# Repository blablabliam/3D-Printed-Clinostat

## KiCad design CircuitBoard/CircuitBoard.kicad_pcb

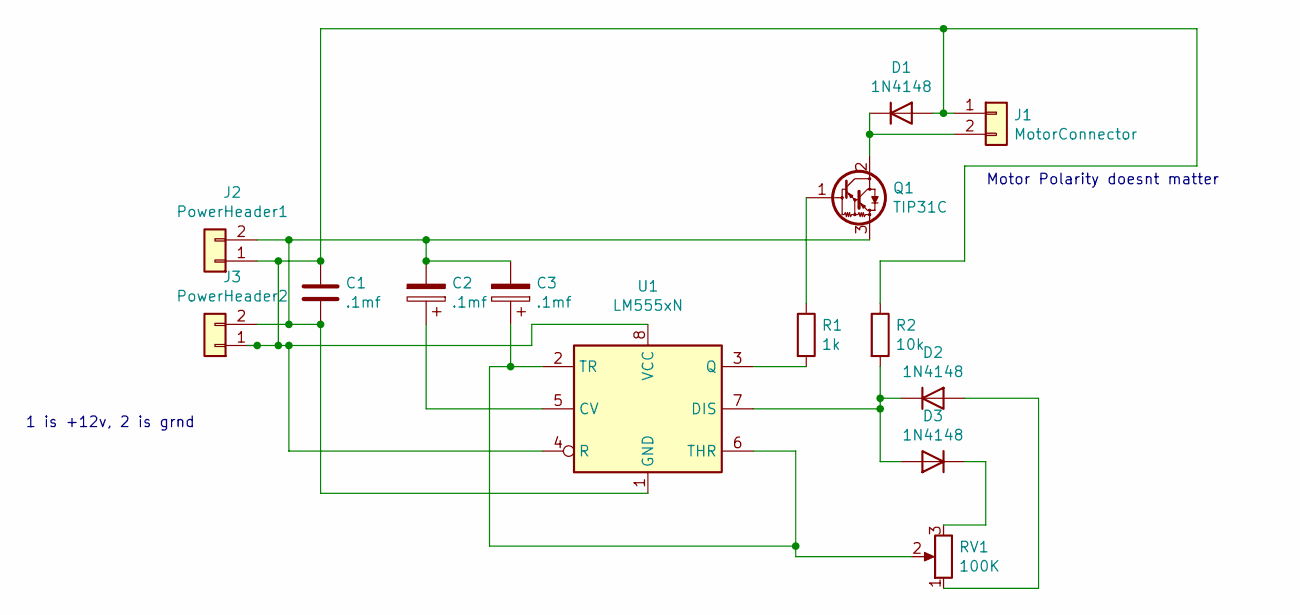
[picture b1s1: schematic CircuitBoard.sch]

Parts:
C1: .1mf; C_Disc_D6.0mm_W2.5mm_P5.00mm
C2, C3: .1mf; CP_Radial_D4.0mm_P2.00mm
D1, D2, D3: 1N4148; D_DO-35_SOD27_P7.62mm_Horizontal
J1: MotorConnector; PinHeader_1x02_P2.54mm_Vertical
J2: PowerHeader1; PinHeader_1x02_P2.54mm_Vertical
J3: PowerHeader2; PinHeader_1x02_P2.54mm_Vertical
Q1: TIP31C; TO-220-3_Vertical
R1: 1k; R_Axial_DIN0207_L6.3mm_D2.5mm_P7.62mm_Horizontal
R2: 10k; R_Axial_DIN0207_L6.3mm_D2.5mm_P7.62mm_Horizontal
RV1: 100K; PinHeader_1x03_P2.54mm_Vertical
U1: LM555xN; DIP-8_W7.62mm

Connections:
unnamed: C1.1, D1.2 (A), J1.1, J2.1, J3.1, R2.1, U1.4 (R), U1.8 (VCC)
unnamed: C1.2, C2.2, C3.2, J2.2, J3.2, Q1.3 (E), U1.1 (GND)
unnamed: C2.1, U1.5 (CV)
unnamed: C3.1, RV1.2, U1.2 (TR), U1.6 (THR)
unnamed: D1.1 (K), J1.2, Q1.2 (C)
unnamed: D2.1 (K), D3.2 (A), R2.2, U1.7 (DIS)
unnamed: D2.2 (A), RV1.1
unnamed: D3.1 (K), RV1.3
unnamed: Q1.1 (B), R1.1
unnamed: R1.2, U1.3 (Q)

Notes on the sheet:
1 is +12v, 2 is grnd
Motor Polarity doesnt matter

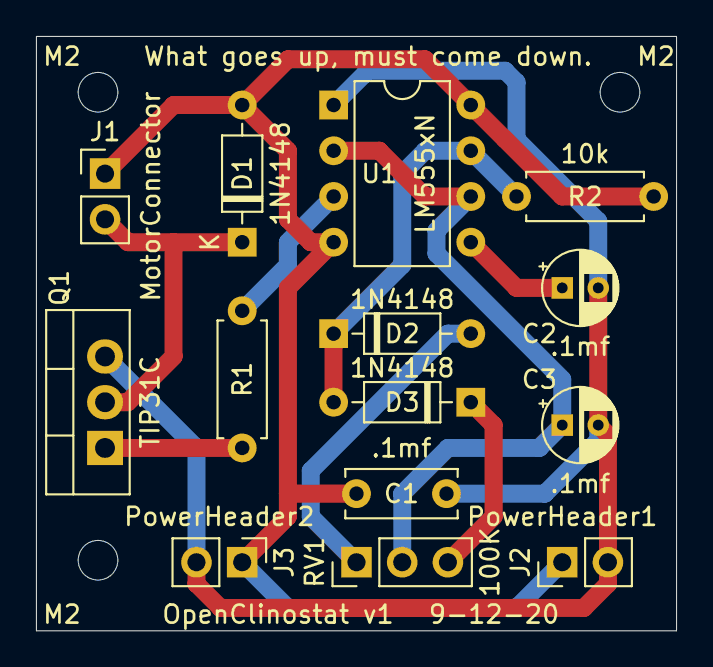
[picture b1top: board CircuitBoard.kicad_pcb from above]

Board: 2 copper layers, 35.6 x 33.0 mm, 17 parts (0 on the bottom side), 10 nets.

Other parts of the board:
M2: 1; MountingHole_2.2mm_M2
M2#2: 2; MountingHole_2.2mm_M2
M2#3: 3; MountingHole_2.2mm_M2

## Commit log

2020-05-26 :space_invader: Added .gitattributes
2020-09-10 Created a schematic of the motor driver
2020-09-14 Finished OpenClinostat v1 Board
    This update contains all of the schematics needed to print the V1 board.
    The board is labled with all of the parts needed, and where all of the
    wires should be connected.
2020-12-05 Fixed an issue in the V1 Board
    New files in the 'second try' folder.
